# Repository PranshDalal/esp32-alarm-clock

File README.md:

# ESP32 Alarm Clock

A Wi-Fi alarm clock built on an ESP32. It gets the time from NTP, with automatic US Pacific daylight-saving changes, shows it on a 128×64 OLED, and lets you set the alarm with two buttons. The alarm is saved in flash, so it survives power cuts. It runs on a custom two-layer PCB I designed in KiCad.

## Features

- **NTP time** from `pool.ntp.org` / `time.nist.gov`, with the time zone `PST8PDT,M3.2.0,M11.1.0`
- **Two-button interface:**
  - SET steps through hour → minute → save
  - \+ changes the value, or toggles the alarm on/off from the clock screen
  - Hold + to auto-repeat (after 500 ms, then every 120 ms)
- **Debounced buttons** (30 ms), timed with `millis()`
- **Alarm saved** in ESP32 flash (NVS) using `Preferences`
- **Ringing:** SET stops it, + snoozes for 5 minutes, and it stops by itself after 3 minutes
- **Rings exactly once per alarm minute.** The firing minute is stamped, so stopping the alarm can't re-trigger it within the same minute.

## How it works

```
NTP servers ──Wi-Fi──► ESP32 ──I2C (GPIO 21/22)──► SSD1306 OLED
                        │ ▲
          GPIO 18 ──────┘ └────── GPIO 19 / 23
          Buzzer                   SET / + buttons
                        │
                        ▼
                  NVS flash (saved alarm)
```

- **Timekeeping:** on boot the ESP32 joins Wi-Fi and calls `configTzTime()`. After that, the ESP32's clock keeps time and NTP keeps it in sync, including daylight-saving changes.
- **Main loop:** timed with `millis()`. Each pass reads and debounces the buttons, updates the menu state, redraws the OLED, and checks whether the current minute matches the alarm.

## Hardware

| Part | Connection |
|---|---|
| ESP32 dev board (on 2× 1×19 pin sockets) | n/a |
| SSD1306 128×64 I2C OLED (address `0x3C`) | SDA → GPIO 21, SCL → GPIO 22 |
| SET button | GPIO 19 (internal pull-up, active low) |
| \+ button | GPIO 23 (internal pull-up, active low) |
| Buzzer | GPIO 18 (active low; change `BUZZER_ACTIVE_LOW` if yours is active high) |

The PCB has headers for the OLED (4-pin) and buzzer (3-pin), screw terminals for the two buttons, and four M3 mounting holes.

## Repository layout

```
firmware/esp_alarm_clock/
  esp_alarm_clock.ino     Arduino sketch
pcb/
  alarm_clock_pcb.kicad_pro / .kicad_sch / .kicad_pcb   KiCad 10 project
  gerbers/                Fabrication files (Gerbers + drill)
  alarm_clock_pcb.step    3D model of the board
  *.pdf                   Copper and board-outline plots
```

## Getting started

### Firmware

1. Install the **ESP32 board package** in the Arduino IDE (Boards Manager → "esp32" by Espressif).
2. Install the libraries **Adafruit SSD1306** and **Adafruit GFX** (Library Manager).
3. Create `firmware/esp_alarm_clock/secrets.h` with your Wi-Fi details. The file is git-ignored.
   ```cpp
   #pragma once
   const char* WIFI_SSID = "your-network";
   const char* WIFI_PASS = "your-password";
   ```
4. Open `esp_alarm_clock.ino`, select your ESP32 board and port, and upload.

To change the time zone, edit `TIMEZONE` near the top of the sketch. It takes a [POSIX TZ string](https://github.com/nayarsystems/posix_tz_db/blob/master/zones.csv).

### PCB

Zip the contents of `pcb/gerbers/` and upload the zip to a PCB fab (JLCPCB, PCBWay, OSH Park and others). The board is two layers, 1.6 mm thick.

## Tech stack

**Firmware:** Arduino (C++), Espressif arduino-esp32 core (`WiFi`, `Preferences`, SNTP), Adafruit SSD1306, Adafruit GFX
**PCB:** KiCad 10

## Credits

- **Adafruit SSD1306** and **Adafruit GFX** libraries by Adafruit (BSD License).
- Schematic symbols and footprints from KiCad's standard libraries.

## AI disclosure

AI assistance (Claude) was used in this project for documentation, testing, and debugging.

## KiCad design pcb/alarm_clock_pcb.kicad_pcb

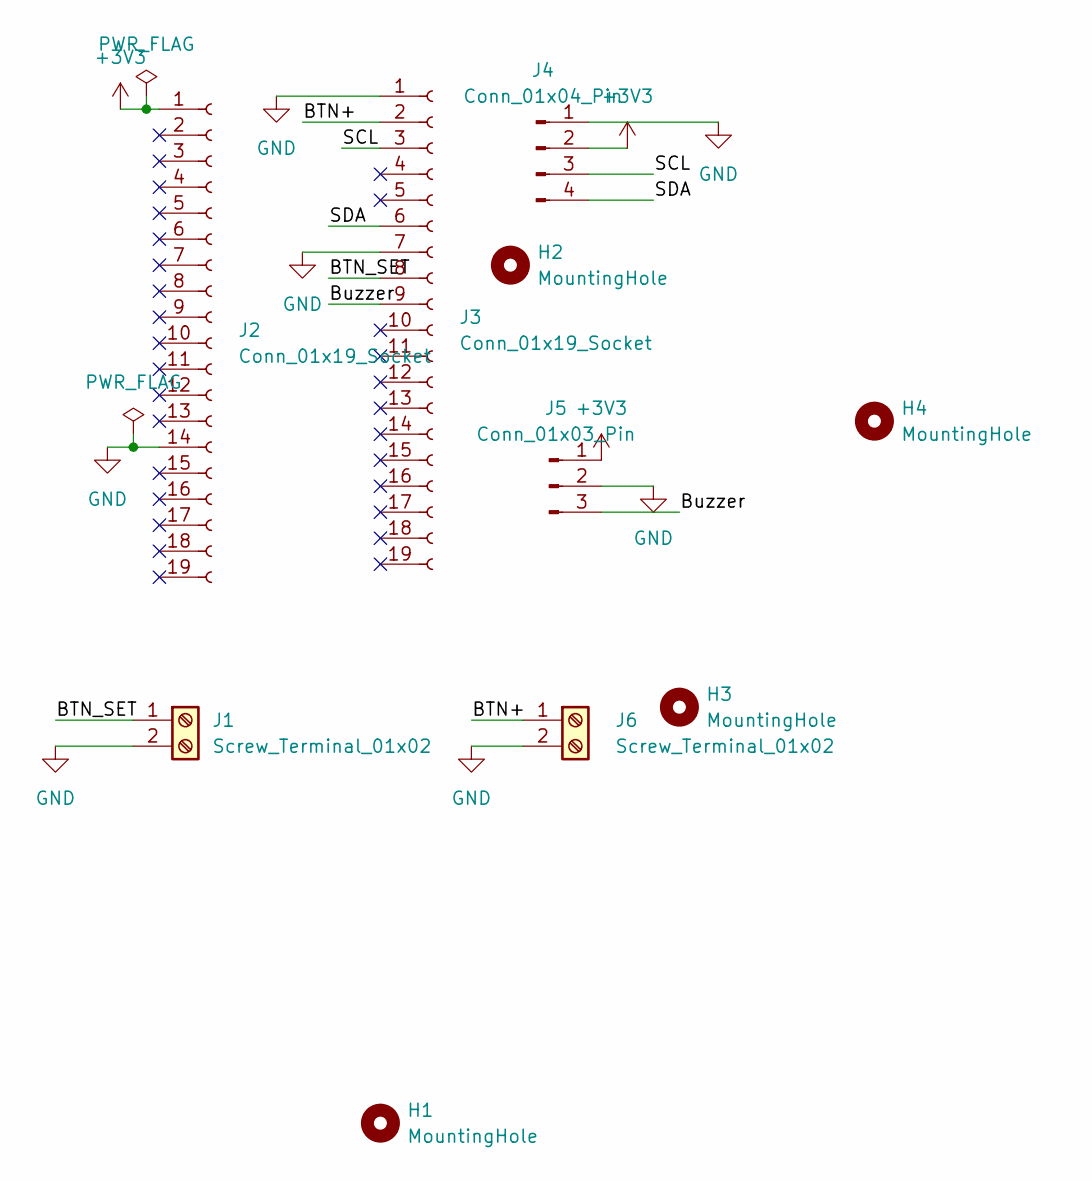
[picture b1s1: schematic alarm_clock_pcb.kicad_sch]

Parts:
H1, H2, H3, H4: MountingHole; MountingHole_3.2mm_M3
J1, J6: Screw_Terminal_01x02; TerminalBlock_Phoenix_MKDS-1,5-2-5.08_1x02_P5.08mm_Horizont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
J2, J3: Conn_01x19_Socket; PinSocket_1x19_P2.54mm_Vertical
J4: Conn_01x04_Pin; PinHeader_1x04_P2.54mm_Vertical
J5: Conn_01x03_Pin; PinHeader_1x03_P2.54mm_Vertical

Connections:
+3V3: J2.1, J4.2, J5.1
/BTN+: J3.2, J6.1
/BTN_SET: J1.1, J3.8
/Buzzer: J3.9, J5.3
/SCL: J3.3, J4.3
/SDA: J3.6, J4.4
GND: J1.2, J2.14, J3.1, J3.7, J4.1, J5.2, J6.2

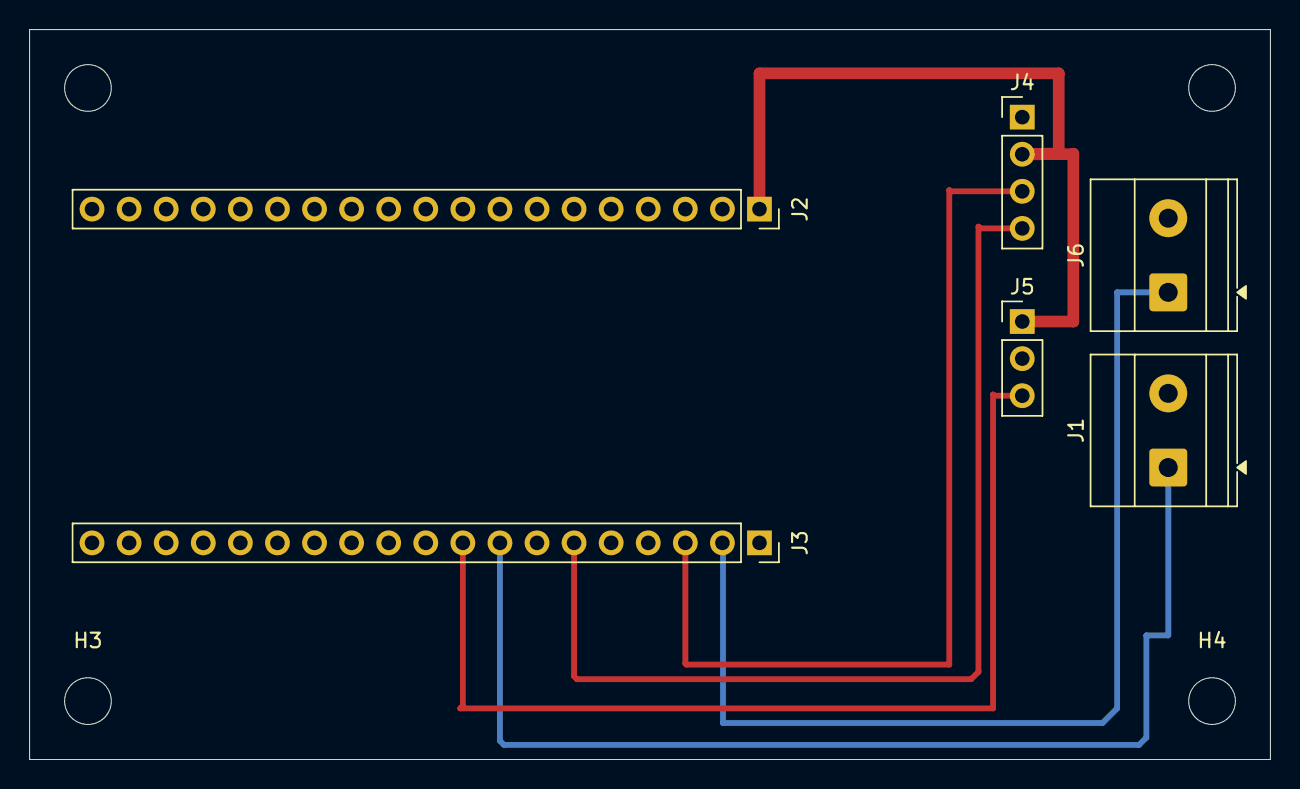
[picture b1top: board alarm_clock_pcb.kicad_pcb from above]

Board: 2 copper layers, 85.0 x 50.0 mm, 10 parts (0 on the bottom side), 7 nets.
